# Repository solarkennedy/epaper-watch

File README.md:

# epaper-watch

Originally setup as a watch, this turned into a wall clock:

It uses a [database of literary quotes](https://xkyle.com/epaper-watch-Cleaning-the-Literary-Quotes-Database/) to display what time it is, highlighting the quote in <font color="red">red</font>.

This project originally started as a wrist watch with battery management and a custom PCB:

The wrist watch version was too ambitious and too distracting, so I gave up and just left it as a wall-clock. Originally I took inspiration from this [clock that used a kindle](https://www.instructables.com/id/Literary-Clock-Made-From-E-reader/), but wanted more control over the hardware.

## Hardware

* 2.9inch (296x128 pixels) Waveshare eink [module](https://www.waveshare.com/wiki/2.9inch_e-Paper_Module_(B))
* esp8266 development board
* Picture frame

## Software

* [Source code](https://github.com/solarkennedy/epaper-watch)
* NTP-sourced time
* Ubuntu font
* Literary quotes for (most) minute of the hour

## Usage

It isn't the most accurate or easy to read clock, but it is interesting and looks nice when it has a good quote on it.

The refresh is a bit ugly and could be improved (click for the youtube version):

The tri-color epaper requires two refresh cycles, one to clear the screen and put down black, then a second pass for the red. See [Ben Krasnow's (Applied Science) notes](https://benkrasnow.blogspot.com/2017/10/fast-partial-refresh-on-42-e-paper.html) on these epaper displays for some interesting low-level technical details on how they work.

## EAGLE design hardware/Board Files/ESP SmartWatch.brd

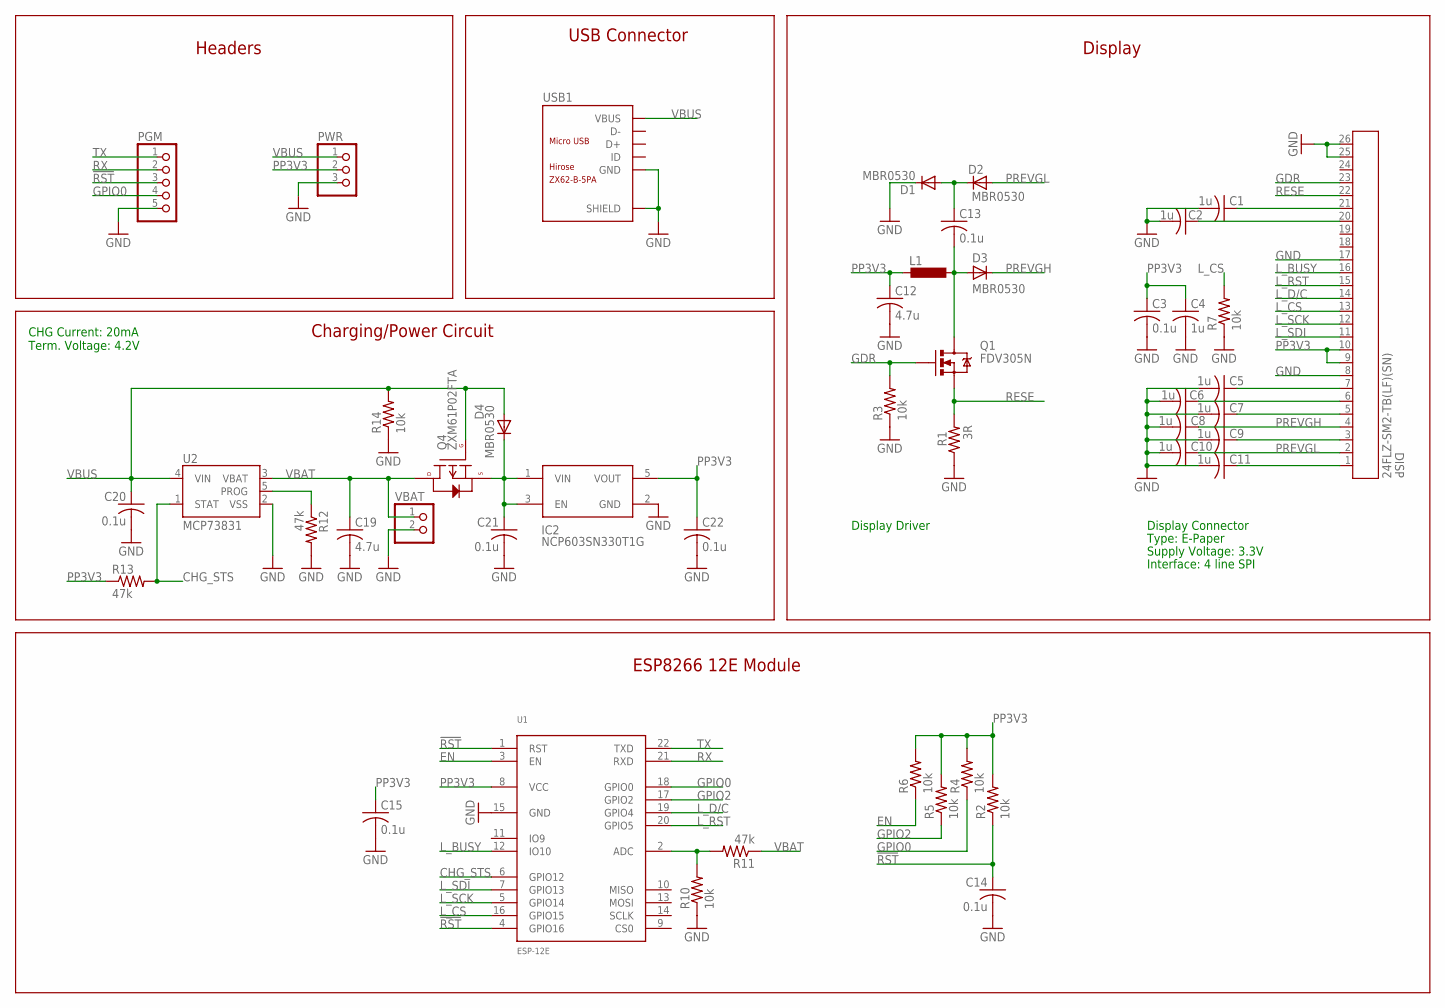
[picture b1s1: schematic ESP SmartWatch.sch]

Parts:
C1, C2, C4, C5, C6, C7, C8, C9, C10, C11: 1u; C0603
C3, C13, C14, C15, C20, C21, C22: 0.1u; C0603
C12, C19: 4.7u; C0603
D1, D2, D3, D4: MBR0530; SOD123
DISP: 24FLZ-SM2-TB(LF)(SN); CON24_1X24_DB_JST
IC2: NCP603SN330T1G; SOT95P275X110-5N
L1: ASPI-6045S-680M-T
PGM: PINHD-1X05_2.00; 1X05M
PWR: PINHD-1X03_2.00; 1X03M
Q1: FDV305N; SOT23-3
Q4: ZXM61P02FTA; SOT23-3
R1: 3R; R0603
R2, R3, R4, R5, R6, R7, R10, R14: 10k; R0603
R11, R12, R13: 47k; R0603
U1: ESP-12E; ESP-12F
U2: MCP73831; SOT23-5
USB1: ZX62-B-5PA; MICRO-USB5+6P-SMD-0.65-AB
VBAT: PINHD-1X02_2.00; 1X02M

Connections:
!RST: C14.1, PGM.3, R2.1, U1.1 (RST), U1.4 (GPIO16)
CHG_STS: R13.2, U1.6 (GPIO12), U2.1 (STAT)
EN: R6.1, U1.3 (EN)
GDR: DISP.23 (2323), Q1.1 (G), R3.2
GND: C1.2, C2.2, C3.2, C4.2, C5.2, C6.2, C7.2, C8.2, C9.2, C10.2, C11.2, C12.2, C14.2, C15.2, C19.2, C20.2, C21.2, C22.2, D1.C, DISP.8 (88), DISP.17 (1717), DISP.25 (2525), DISP.26 (2626), IC2.2 (GND), PGM.5, PWR.3, R1.1, R3.1, R7.1, R10.1, R12.2, R14.1, U1.15 (GND), U2.2 (VSS), USB1.5 (GND), USB1.P1 (SHIELD), USB1.P2 (SHIELD), USB1.P3_1 (SHIELD), USB1.P3_2 (SHIELD), USB1.P3_3 (SHIELD), USB1.P4_1 (SHIELD), USB1.P4_2 (SHIELD), USB1.P4_3 (SHIELD), USB1.P5 (SHIELD), USB1.P6 (SHIELD), VBAT.2
GPIO0: PGM.4, R4.1, U1.18 (GPIO0)
GPIO2: R5.1, U1.17 (GPIO2)
L_BUSY: DISP.16 (1616), U1.12 (IO10)
L_CS: DISP.13 (1313), R7.2, U1.16 (GPIO15)
L_D/C: DISP.14 (1414), U1.19 (GPIO4)
L_RST: DISP.15 (1515), U1.20 (GPIO5)
L_SCK: DISP.12 (1212), U1.5 (GPIO14)
L_SDI: DISP.11 (1111), U1.7 (GPIO13)
unnamed: C1.1, DISP.21 (2121)
unnamed: C2.1, DISP.20 (2020)
unnamed: C13.1, D1.A, D2.C
unnamed: C13.2, D3.A, L1.2, Q1.3 (D)
unnamed: R10.2, R11.2, U1.2 (ADC)
unnamed: R12.1, U2.5 (PROG)
unnamed: C21.1, D4.C, IC2.1 (VIN), IC2.3 (EN), Q4.2 (S)
unnamed: C5.1, DISP.7 (77)
unnamed: C6.1, DISP.6 (66)
unnamed: C7.1, DISP.5 (55)
unnamed: C9.1, DISP.3 (33)
unnamed: C11.1, DISP.1 (11)
PP3V3: C3.1, C4.1, C12.1, C15.1, C22.1, DISP.9 (99), DISP.10 (1010), IC2.5 (VOUT), L1.1, PWR.2, R2.2, R4.2, R5.2, R6.2, R13.1, U1.8 (VCC)
PREVGH: C8.1, D3.C, DISP.4 (44)
PREVGL: C10.1, D2.A, DISP.2 (22)
RESE: DISP.22 (2222), Q1.2 (S), R1.2
RX: PGM.2, U1.21 (RXD)
TX: PGM.1, U1.22 (TXD)
VBAT: C19.1, Q4.3 (D), R11.1, U2.3 (VBAT), VBAT.1
VBUS: C20.1, D4.A, PWR.1, Q4.1 (G), R14.2, U2.4 (VIN), USB1.1 (VBUS)

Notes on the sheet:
Display Connector
Interface: 4 line SPI
Supply Voltage: 3.3V
Type: E-Paper
Display Driver
Display
USB Connector
Charging/Power Circuit
ESP8266 12E Module
Headers
CHG Current: 20mA Term. Voltage: 4.2V

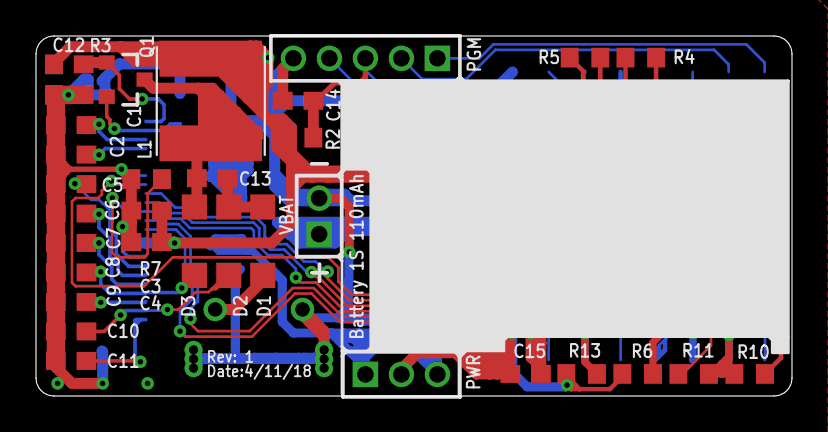
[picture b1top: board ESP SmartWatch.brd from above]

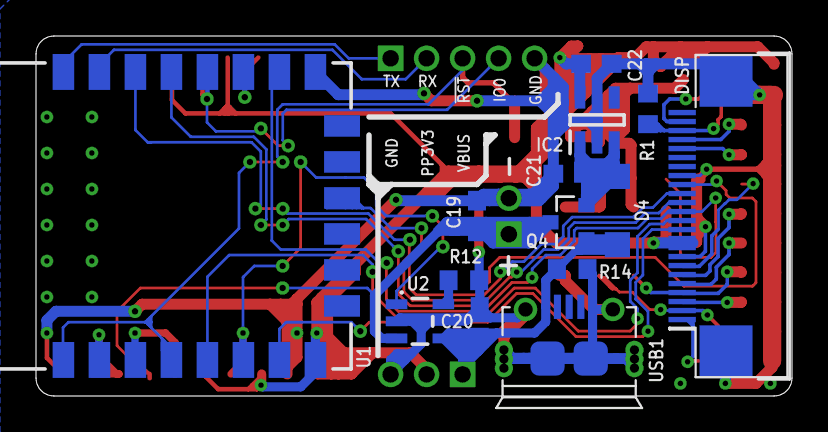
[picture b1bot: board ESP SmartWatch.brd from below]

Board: 2 copper layers, 42.0 x 20.0 mm, 46 parts (14 on the bottom side), 33 nets.

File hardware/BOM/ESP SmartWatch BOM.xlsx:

| ESP SmartWatch Bill of Materials
 | Qty | Part | Value | Device | Package | MPN
 | 10 | C1, C2, C4, C5, C6, C7, C8, C9, C10, C11 | 1u | C-USC0603 | C0603 | CL10B105MO8NNWC
 | 7 | C3, C13, C14, C15, C20, C21, C22 | 0.1u | C-USC0603 | C0603 | CL10F104ZO8NNNC
 | 2 | C12, C19 | 4.7u | C-USC0603 | C0603 | CL10A475KP8NNNC
 | 4 | D1, D2, D3, D4 | MBR0530 | MBR0520LT | SOD123 | MBR0530
 | 1 | DISP | 24FLZ-SM2-TB(LF)(SN) | 24FLZ-SM2-TB(LF)(SN) | CON24_1X24_DB_JST | 24FLZ-SM2-TB(LF)(SN)
 | 1 | IC2 | NCP603SN330T1G | NCP603SN330T1G | SOT95P275X110-5N | NCP603SN330T1G
 | 1 | L1 | ASPI-6045S-680M-T | ASPI-6045S-680M-T | ASPI-6045S-680M-T | ASPI-6045S-680M-T
 | 1 | Q1 | FDV305N | MOSFET-NCH | SOT23-3 | FDV305N
 | 1 | Q4 | ZXM61P02FTA | MOSFET-PCH | SOT23-3 | ZXM61P02FTA
 | 1 | R1 | 3R | R-US_R0603 | R0603 | RC0603FR-073R01L
 | 8 | R2, R3, R4, R5, R6, R7, R10, R14 | 10k | R-US_R0603 | R0603 | RC0603FR-0710KL
 | 3 | R11, R12, R13 | 47k | R-US_R0603 | R0603 | RC0603FR-0747KL
 | 1 | U1 | ESP-12F | ESP-12F | ESP-12F | *module*
 | 1 | U2 | MCP73832 | MCP73832 | SOT23-5 | MCP73832T-2ACI/OT
 | 1 | USB1 | ZX62-B-5PA | MICRO-USB-SMD(ZX62-B-5PA) | MICRO-USB | ZX62-B-5PA(33)

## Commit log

2018-09-30 Added avr lib
2018-09-30 Use esp instead of 32 for pgmspace
2018-09-30 Remove sdcard stuff
2018-10-01 working epaper lib
2018-10-01 copy over epaper demo
2018-10-01 codegen phase 1 for lit stuff
2018-10-02 Working on both avr and esp32
2018-10-02 Removed unused imagedata
2018-10-02 Working serial output of quotes
2018-10-14 real printing and csv cleanup
2018-10-28 more csv changes and stuff
2018-10-28 Ensure all csv time strings exist
2018-10-28 Sanitize attribution string
2018-11-03 stuff
2018-11-03 Working compile plus ntp
2018-11-04 Simpler startup
2018-11-04 Some power management
2018-11-04 Working epaper driver port
2018-11-04 Working display with GxGD lib
2018-11-05 Working text with GxGD
2018-11-05 Added hardware files
2018-11-11 More lit tweaks
2018-11-11 Semi-working rtc syncing
2018-12-02 Almost working OTA
2019-01-01 Working battery meter
2019-02-18 Removed ota code
2019-02-18 Better main logic to sync time first
2019-02-24 Vendor in the Ubuntu font
2019-02-24 Use a global quote variable to save ram
2019-02-24 Set the quote to the current time when there is none
2019-02-25 Swtich to EPD2
2019-02-25 Handle the attribution string for the quote
2019-02-25 Handle local timezone
2019-02-25 Added attribution when there is no quote
2019-02-25 More wifi ntp sync + power optimiziations
2019-02-28 Working word-wrap code
2019-02-28 Sorta working bold on the timestring
2019-03-30 Removed extra spaces from csv
2019-03-30 Massive cleanup on the lit csv
2019-03-31 Massive editing of the quote database
2019-03-31 No quotes more than 180 characters
2019-03-31 Replace non-ascii chars out of the csv
2019-04-01 More accurate battery reading
2019-05-27 Duplicate out all the quotes that have ambiguous AM/PM
2019-05-27 Expand the lit database to include am/pm duplicates for real
2019-09-18 Massive quote fixes
2019-09-18 Better wifi and red colors
2019-09-19 Added DEBUG and WATCH directives
2019-09-19 Lots of quote fixes
2019-09-19 Fix DEV and WATCH mode
2019-09-27 Only replace one instance of the bolded quote. Fixes #1
2019-11-10 Added in compile time for debug purposes
2020-02-11 Better sleep in dev mode
2021-12-23 Load creds from file
